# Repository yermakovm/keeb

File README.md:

# keeb split keyboard

This repo is the keyboard's authored code (keymap, shield, drivers, web UI).
It lives inside a Zephyr workspace; upstream (ZMK + Zephyr + vendor HALs) is
downloaded by `west` into the workspace root, never into this repo.

```
keyboard-zmk/                        west workspace root (not a git repo)
├── .west/config                     manifest.path = zmk-config
├── zephyr/                          west project (not in git)
├── zmk/                             west project (not in git)
├── modules/                         west projects (not in git)
├── optional/                        west projects (not in git)
├── out/                             build trees: out/left, out/right
└── zmk-config/                      THIS REPO
    ├── config/                      keeb.keymap + keeb.conf   (ZMK user config)
    ├── keeb-module/                 keeb shield, behaviors, bindings, status
    │                                screen, art, tools   (Zephyr module)
    ├── status-led/                  RGB status LED driver (Zephyr module)
    ├── buzzer/                      active buzzer driver + behavior (Zephyr module)
    ├── west.yml                     manifest (ZMK; local modules via ZMK_EXTRA_MODULES)
    ├── Makefile  env.mk             build + flash entry points
    ├── env.sh                       shell env (SDK, west, ZMK_CONFIG, module paths)
    ├── build.sh                     build one half, show errors + memory usage
    ├── docs/                        presentation deck (Marp slides, Ukrainian),
    │                                theme/keeb.css, build.mjs (merges <n>_*.md
    │                                into one deck), assets/
    └── package.json                 deck toolchain (marp-cli devDependency)
```

## Build

```sh
make -C zmk-config left        # -> out/left
make -C zmk-config right       # -> out/right
```
Or `./build.sh left|right` from this directory (same build, prints only errors
and the memory-usage table). A raw `west build` works too:

```sh
source zmk-config/env.sh
west build -s zmk/app -b nice_nano@2.0.0//zmk -d out/left -- \
     -DSHIELD=keeb_left -DZMK_CONFIG="$ZMK_CONFIG" \
     -DZMK_EXTRA_MODULES="$KEEB_MODULE;$STATUS_LED;$BUZZER"
```

## Flash (UF2)

```sh
make -C zmk-config flash-right     # or flash-left
```
## Live keymap engine (KEEB TLV over BLE GATT)

The keyboard accepts a binary config channel over BLE GATT and rebinds keys,
renames/reorders/adds/removes layers and persists the result — written from
scratch. **ZMK Studio is not used**: its protobuf RPC, subsystem/handler linker
sections, transports and locking are not enabled and not compiled. What is
reused is ZMK's *core* dynamic keymap (`CONFIG_ZMK_KEYMAP_SETTINGS_STORAGE`,
`CONFIG_ZMK_KEYMAP_LAYER_REORDERING`) — the same options Studio merely selects,
which is what makes this the same feature without Studio.

Engine code lives in `keeb-module/`:

```
proto/keeb_tlv.h|.c          packet header + record codec, fragmentation,
                             reassembly, CRC-32/IEEE. Plain C, no Zephyr
                             headers, so the host test links the same file
engine/keeb_engine.c         dispatcher: one RX slot, one work item, reply =
                             ACK record + response records, notify queue
keymap/keeb_tokens.c         token table generated from devicetree, name hash
keymap/keeb_keymap.c         the ONLY file allowed to call ZMK's keymap core
transport/keeb_ble.c         vendor GATT service (write/notify), MTU-aware
```

`keymap/keeb_keymap.c` being the single ZMK-core entry point is deliberate:
after a ZMK rebase, that is the one file to re-audit.

**Wire format.** 16-byte little-endian packet header
(`magic | version | flags | msg_id | frag_off | frag_len | msg_len | crc32`),
payload = records of `type(u16) | len(u16) | value`. A message is up to
`KEEB_TLV_MSG_MAX` (1024 B) bytes and is fragmented by the sender to
`CONFIG_BT_L2CAP_TX_MTU - 3 - 16` (46 B: the ATT opcode and handle, and the
packet header itself, all of which live inside the notification), so a 700-byte
keymap dump travels as sixteen notifications. The peer's real MTU is checked per
connection before a fragment is handed to `bt_gatt_notify`, because Zephyr
reports an oversized PDU as `-ENOMEM` - the same code an empty TX pool gives,
and the wrong reason to retry the same bytes. Records are applied in order, and the reply carries an ACK record
as record 0 plus the response records; a failure in one record is reported as
the ACK code while earlier records stay applied — only `CELLS_SET` is
all-or-nothing (validate every cell with `zmk_behavior_validate_binding` first,
then write), so no half-accepted layout can arrive. Reassembly requires
in-order offsets: a gap makes the receiver refuse with `KEEB_ERR_BAD_SEQ` and
the sender restarts the message with `KEEB_PKT_F_FIRST`, which keeps the
receiver stateless about losses. A reply that never arrives means the host
restarts the message.

**Tokens.** A binding cannot be named by string alone (`zmk_behavior_get_binding`
resolves device names that exist in the image), so the protocol references
*tokens*: the devicetree `tokens` list on the `keeb,engine` node, id = index in
that list. The engine reports the table plus a CRC-32 over
`u16 id | name | 0x00` per token, and the host must echo that hash before any
write is accepted — host and firmware can never silently disagree about what a
token means. Behaviors whose driver was dropped by Kconfig stay in devicetree
and are reported as unavailable, so a write can never be answered with a token
the firmware cannot execute.

**Escape hatch.** `reserved-positions` on the `keeb,engine` node (`KEEB_POS_L_TOP_0`
and `KEEB_POS_R_TOP_0` in `keeb-module/dts/keeb-positions.dtsi` — positions 0 and 11,
the outer top corners, `&kp EQUAL` / `&kp MINUS` in the stock keymap) are refused
by the engine (`KEEB_ERR_RESERVED_POSITION`), so a layout from the configurator
can never take away the revert chord. Holding *all* reserved positions for
`revert-hold-ms` (3 s) runs `keeb_keymap_discard()`, i.e. ZMK's
`zmk_keymap_discard_changes()`: unsaved changes are dropped and the keyboard
returns to its saved overlay (the keymap file when nothing is saved). It is
detected on raw key positions, so no layout — and no broken or missing layout —
can lock the configurator out. Clearing a *saved* layout without the app needs
`keeb_keymap_reset()`, which the chord does not call today.
Persistence is ZMK's own:
`SAVE` / `DISCARD` / `RESET` go to `zmk_keymap_save_changes()`,
`zmk_keymap_discard_changes()`, `zmk_keymap_reset_settings()`.

**Central-only by design** (`CONFIG_KBEEB_ENGINE depends on !ZMK_SPLIT ||
ZMK_SPLIT_ROLE_CENTRAL`): ZMK resolves bindings on the central and sends the
resolved binding to the peripheral, so the peripheral executes whatever the
central's layout says, and it holds no host connection anyway. The right half
builds without a single engine symbol.

## Editing the panel from the app

The live configurator (`app/`) edits this table over the same KEEB TLV channel
as the keymap, in the `DISPLAY` namespace that the protocol reserved from the
start:

| record | what it does |
|---|---|
| `DISPLAY_INFO` | the real limits: widget count, slot count, slot length, kind/source range, logical vs panel size, rotation, `sizeof(keeb_widget)`, layer count, whether artwork is drawable |
| `PRESET_NAME` | one per preset, so the picker is built from the keyboard |
| `DISPLAY_GET` → `DISPLAY` | the table, then the text slots and value slots as their own records |
| `DISPLAY_SET` | replace the whole table (validated as a unit: nothing is drawn if one entry is bad) |
| `WIDGET_SET` | replace or append one entry |
| `TEXT_SET` / `VALUE_SET` | write a host-owned slot |
| `PRESET_SET` | restore a compiled-in preset, including its own text |
| `DISPLAY_SAVE` / `DISPLAY_DISCARD` / `DISPLAY_RESET` | persist / revert / delete the saved panel |
| `DISPLAY_BLANK` | clear the glass once, on the next paint |

Applying and persisting stay two operations, exactly as in the keymap: a
`DISPLAY_SET` redraws the panel now, and only `DISPLAY_SAVE` survives a reboot
or a deep sleep. `SYS INFO` advertises `KEEB_INFO_F_DISPLAY` so a configurator
can tell a panel-capable build from one that is not.

Image upload (`KEEB_NS_IMAGE`) is still unimplemented: the panel today selects
compiled-in artwork, it does not receive bitmaps.

## Presentation deck (docs/)

`docs/<n>_*.md` are Marp slides; `docs/theme/keeb.css` is
the deck theme (dark palette, 16:9 1280x720). Marp CLI is a devDependency, so there is
nothing global to install:

```sh
npm run deck        # -> docs/dist/deck.html + deck.pdf
npm run deck:html   # HTML only (self-contained, presents offline)
npm run deck:pdf    # PDF only
npm run preview     # live preview of the title slide

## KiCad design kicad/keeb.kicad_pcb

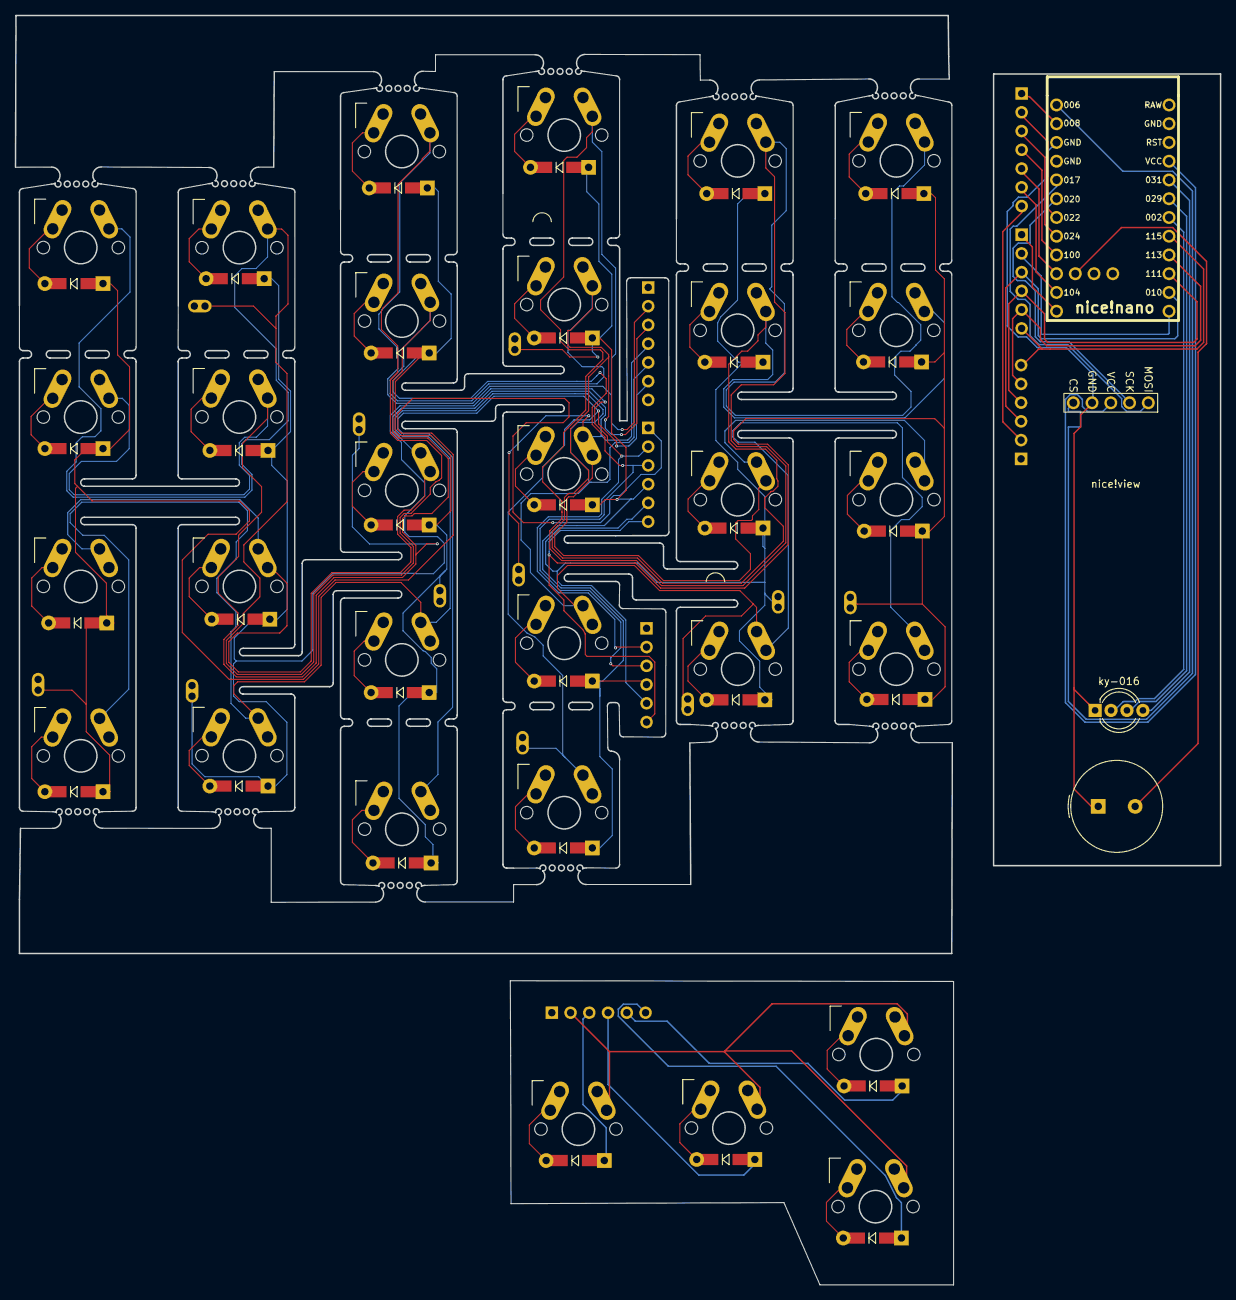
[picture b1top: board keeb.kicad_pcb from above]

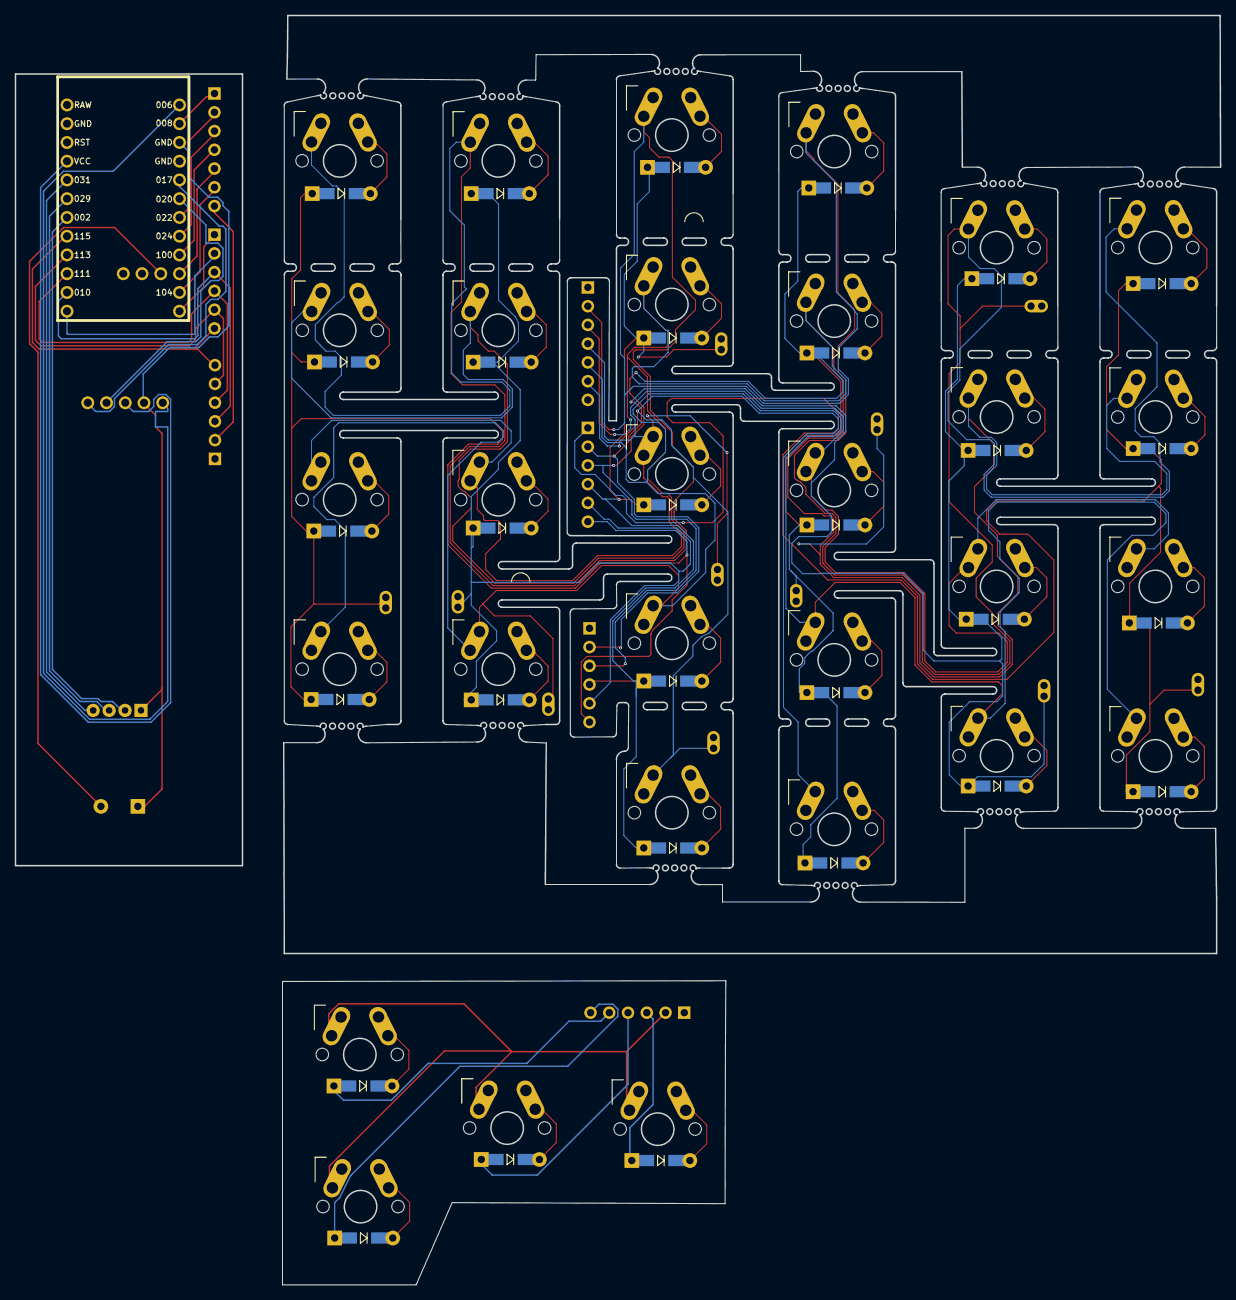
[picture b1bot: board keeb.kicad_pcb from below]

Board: 2 copper layers, 126.9 x 127.1 mm, 82 parts (60 on the bottom side), 48 nets.

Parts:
D1, D2, D3, D4, D5, D6, D7, D8, D9, D10, D11, D12, D13, D14, D15, D16, D17, D18, D19, D20, D21, D22, D23, D24, D25, D25#2, D25#3, D25#4, D25#5, D26: D; Diode_TH_SOD123
J1, J14, J14#2, J14#3, J14#4: Conn_01x06_Female; PinSocket_1x06_P2.54mm_Vertical
J2, J2#2: Conn_01x07_Female; PinSocket_1x07_P2.54mm_Vertical
J4, J5, J6, J7, J8, J9, J10, J11, J12, J13, J15: Conn_01x02_Female; SolderWire-0.15sqmm_1x01_D0.5mm_OD1.5mm
SW1, SW2, SW3, SW4, SW5, SW6, SW7, SW8, SW9, SW10, SW11, SW12, SW13, SW14, SW15, SW16, SW17, SW18, SW19, SW20, SW21, SW22, SW23, SW24, SW25, SW25#2, SW25#3, SW25#4, SW25#5, SW26: SW_Push; SW_MX_reversible
U1: nice_nano
display: nice!view; nice_view
ky-016: buzzer; LED_D5.0mm-4_RGB_Wide_Pins
ky-040: Buzzer_TDK_PS1240P02BT_D12.2mm_H6.5mm

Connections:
GND: U1.3, U1.23, display.4, ky-016.1, ky-040.1
unnamed: D1.2 (A), SW1.2
unnamed: D2.2 (A), SW2.2
unnamed: D3.2 (A), SW3.2
unnamed: D4.2 (A), SW4.2
unnamed: D5.2 (A), SW5.2
unnamed: D6.2 (A), SW6.2
unnamed: D7.2 (A), SW7.2
unnamed: D8.2 (A), SW8.2
unnamed: D9.2 (A), SW9.2
unnamed: D10.2 (A), SW10.2
unnamed: D11.2 (A), SW11.2
unnamed: D12.2 (A), SW12.2
unnamed: D13.2 (A), SW13.2
unnamed: D14.2 (A), SW14.2
unnamed: D15.2 (A), SW15.2
unnamed: D16.2 (A), SW16.2
unnamed: D17.2 (A), SW17.2
unnamed: D18.2 (A), SW18.2
unnamed: D19.2 (A), SW19.2
unnamed: D20.2 (A), SW20.2
unnamed: D21.2 (A), SW21.2
unnamed: D22.2 (A), SW22.2
unnamed: D23.2 (A), SW23.2
unnamed: D24.2 (A), SW24.2
unnamed: D25.2 (A), D25#2.2 (A), D25#3.2 (A), D25#4.2 (A), D25#5.2 (A), SW25.2, SW25#2.2, SW25#3.2, SW25#4.2, SW25#5.2
unnamed: D26.2 (A), SW26.2
VCC: U1.21, display.3
b: U1.20, ky-016.4
buz: U1.31, ky-040.2
col1: D1.1 (K), D2.1 (K), D3.1 (K), D4.1 (K), J9.1 (Pin_1_1), J14#2.1, J14#4.1, U1.12
col2: D5.1 (K), D6.1 (K), D7.1 (K), D8.1 (K), J1.2, J10.1 (Pin_1_1), J14#2.2, J14#4.2, U1.13
col3: D9.1 (K), D10.1 (K), D11.1 (K), D12.1 (K), D13.1 (K), D25#2.1 (K), J1.3, J11.1 (Pin_1_1), J14.3, J14#2.3, J14#3.3, J14#4.3, U1.14
col4: D14.1 (K), D15.1 (K), D16.1 (K), D17.1 (K), D18.1 (K), D25.1 (K), J1.4, J12.1 (Pin_1_1), J14.4, J14#2.4, J14#3.4, J14#4.4, U1.15
col5: D19.1 (K), D20.1 (K), D21.1 (K), D22.1 (K), D25#4.1 (K), J1.5, J13.1 (Pin_1_1), J14.5, J14#2.5, J14#3.5, J14#4.5, U1.16
col6: D23.1 (K), D24.1 (K), D25#3.1 (K), D25#5.1 (K), D26.1 (K), J1.6, J14.6, J14#2.6, J14#3.6, J14#4.6, J15.1 (Pin_1_1), U1.17
cs: U1.1, display.5
g: U1.19, ky-016.3
mosi: U1.5, display.1
r: U1.18, ky-016.2
row0: J2.1, J2#2.2, J4.1 (Pin_1_1), SW1.1, SW5.1, SW9.1, SW14.1, SW19.1, SW23.1, U1.2 (r0)
row1: J2.2, J2#2.3, J5.1 (Pin_1_1), SW2.1, SW6.1, SW10.1, SW15.1, SW20.1, SW24.1, U1.7
row2: J2.3, J2#2.4, J6.1 (Pin_1_1), SW3.1, SW7.1, SW11.1, SW16.1, SW21.1, SW25#4.1, U1.8
row3: J2.4, J2#2.5, J7.1 (Pin_1_1), SW4.1, SW8.1, SW12.1, SW17.1, SW22.1, SW26.1, U1.9
row4: J2.5, J2#2.6, J8.1 (Pin_1_1), SW13.1, SW18.1, U1.10
row5: J2.6, J14.2, SW25.1, SW25#2.1, SW25#3.1, SW25#5.1, U1.11
row6: J1.1, J2.7, J14#3.2
sck: U1.6, display.2
